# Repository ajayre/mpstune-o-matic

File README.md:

# mpstune-o-matic
D-Jetronic MPS Tune-o-Matic

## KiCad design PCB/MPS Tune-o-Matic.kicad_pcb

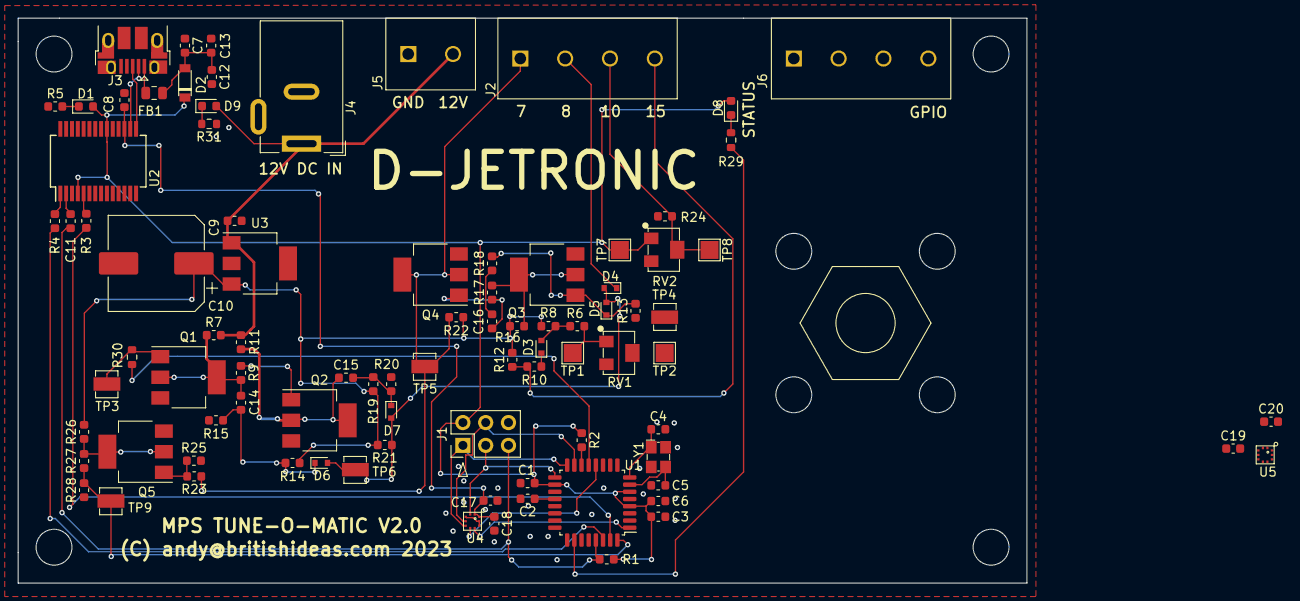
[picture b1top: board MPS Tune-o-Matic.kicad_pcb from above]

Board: 2 copper layers, 112.5 x 63.0 mm, 89 parts (0 on the bottom side), 54 nets.

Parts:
C1, C12: 4.7uF; C_0603_1608Metric
C2, C8, C11, C13, C17, C18, C19, C20: 100nF; C_0603_1608Metric
C3, C6: 1uF; C_0603_1608Metric
C4, C5: 18pF; C_0603_1608Metric
C7: 10nF; C_0603_1608Metric
C9: 0.47uF; C_0603_1608Metric
C10: 22uF; CP_Elec_10x10.5
C14, C15: 6.8n; C_0603_1608Metric
C16: 1.0n; C_0603_1608Metric
D1, D8, D9: APT1608EC; LED_0603_1608Metric
D2: MBR0520LT1G; SOD-123
D3, D4, D5, D6, D7: RB520SM-30T2R; D_SOD-523
FB1: MI0805K400R-10; R_0805_2012Metric
J1: ISP; PinHeader_2x03_P2.54mm_Vertical
J2: MPS; PhoenixContact_COMBICON_PT_4
J3: USB_B_Micro; USB_Micro-B_Amphenol_10103594-0001LF_Horizontal
J4: 12V 1A IN (5.5/2.5); BarrelJack_Wuerth_6941xx301002
J5: 12V IN; PhoenixContact_COMBICON_MKDSN_2
J6: GPIO; PhoenixContact_COMBICON_PT_4
Q1, Q2, Q3, Q4, Q5: PZT2222A,115; SOT-223-3_TabPin2
R1, R2, R3, R4, R7, R11, R22, R24: 1k; R_0603_1608Metric
R5, R29: 150; R_0603_1608Metric
R6: 240; R_0603_1608Metric
R8: 1k2; R_0603_1608Metric
R9, R25, R27, R30: 10k; R_0603_1608Metric
R10: 2k2; R_0603_1608Metric
R12, R31: 510; R_0603_1608Metric
R13: 180k; R_0603_1608Metric
R14, R19: 130k; R_0603_1608Metric
R15, R20: 68k; R_0603_1608Metric
R16, R26: 2k; R_0603_1608Metric
R17: 2k4; R_0603_1608Metric
R18: 300; R_0603_1608Metric
R21: 100k; R_0603_1608Metric
R23: 20k; R_0603_1608Metric
R28: 12k; R_0603_1608Metric
RV1: 1k; Surface_Mount_Cermet_Trimmer_SM-42-43W
RV2: 5k; Surface_Mount_Cermet_Trimmer_SM-42-43W
TP1: AT1; TestPoint_Pad_2.0x2.0mm
TP2: AT2; TestPoint_Pad_2.0x2.0mm
TP3, TP5, TP6, TP9: 5194TR; 5190TR-Colored-Test-Point
TP4: 5195TR; 5190TR-Colored-Test-Point
TP7: BIAS1; TestPoint_Pad_2.0x2.0mm
TP8: BIAS2; TestPoint_Pad_2.0x2.0mm
U1: ATmega328P; LQFP-32_7x7mm_P0.8mm
U2: FT232RL; SSOP-28_5.3x10.2mm_P0.65mm
U3: LM2940; SOT-223
U4, U5: BMP390; LGA-2x2-10-pin
Y1: FA-238 16.0000MB-C3; FA-238

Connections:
+3V3: C8.1, C17.1, C18.1, C19.1, C20.1, U2.17, U4.1, U4.10, U5.1, U5.10
+5V: C1.1, C3.1, C6.1, D1.2, D2.1, D8.2, J1.2, J6.1, R1.1, R2.1, RV2.1, TP7.1, U1.4, U1.6, U1.18, U2.4, U2.20
+10V: C10.1, R8.2, R12.2, R14.2, R16.2, R19.2, R21.2, R22.2, R26.2, U3.3
+12V: C9.1, D9.2, J4.1, J5.2, R7.2, R11.2, U3.1
/INT_PRESSURE: U1.1, U4.7
/INT_VAC_PRESSURE: U1.2, U5.7
/MISO: J1.1, U1.16, U4.5, U5.5
/MOSI: J1.4, U1.15, U4.4, U5.4
/MPS Stimulator/AUX11-TGL: C15.1, Q2.2, R11.1
/MPS Stimulator/AUX12-TGL: C14.1, Q1.2, R7.1, R9.2
/MPS Stimulator/EDGES: D4.2, D5.2, D6.2, D7.2, R21.1, TP6.1
/MPS-7: J2.1, Q4.2, R22.1, R23.1, TP5.1
/MPS-8: D4.1, J2.2
/MPS-10: J2.3, R24.2, RV2.2, TP8.1
/MPS-15: J2.4, R10.1, R12.1
/MPS_PULSE: R27.1, R28.2, TP9.1, U1.32
/MPS_STIMULUS: R30.2, U1.13
/RX: R4.2, U2.1
/SCK: J1.3, U1.17, U4.2, U5.2
/STATUS: R29.1, U1.26
/TX: R3.2, U2.5
/~CS_PRESSURE: U1.12, U4.6
/~CS_VAC_PRESSURE: U1.11, U5.6
/~RESET: C11.1, J1.5, R1.2, U1.29
GND: C1.2, C2.2, C3.2, C4.2, C5.1, C6.2, C7.1, C8.2, C9.2, C10.2, C12.2, C13.2, C17.2, C18.2, C19.2, C20.2, J1.6, J3.4, J3.5, J3.6, J4.2, J4.3, J5.1, J6.4, Q1.3, Q2.3, Q3.3, Q4.3, Q5.3, R5.1, R13.1, R15.1, R20.1, R24.1, R25.2, R28.1, R31.1, RV1.2, TP2.1, TP4.1, U1.3, U1.5, U1.21, U2.7, U2.18, U2.21, U2.25, U2.26, U3.2, U3.4, U4.3, U4.8, U4.9, U5.3, U5.8, U5.9, Y1.2, Y1.4
unnamed: C2.1, U1.20
unnamed: C4.1, U1.8, Y1.1
unnamed: C5.2, U1.7, Y1.3
unnamed: C11.2, U2.2
unnamed: C14.2, D6.1, R14.1, R15.2
unnamed: C15.2, D7.1, R19.1, R20.2
unnamed: C16.1, Q4.1, R17.1
unnamed: C16.2, R18.1
unnamed: D1.1, R5.2
unnamed: D3.1, R10.2
unnamed: D3.2, R6.1, R8.1
unnamed: D5.1, Q3.1, R13.2, R18.2
unnamed: D8.1, R29.2
unnamed: D9.1, R31.2
unnamed: FB1.1, J3.1
unnamed: J3.2, U2.16
unnamed: J3.3, U2.15
unnamed: J6.2, U1.10
unnamed: J6.3, U1.9
unnamed: Q1.1, R30.1, TP3.1
unnamed: Q2.1, R9.1
unnamed: Q3.2, R16.1, R17.2
unnamed: Q5.1, R23.2, R25.1
unnamed: Q5.2, R26.1, R27.2
unnamed: R2.2, U1.14
unnamed: R3.1, U1.31
unnamed: R4.1, U1.30
unnamed: R6.2, RV1.1, TP1.1
VBUS: C7.2, C12.1, C13.1, D2.2, FB1.2

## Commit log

2021-12-06 Started schematic.
2021-12-07 WIP.
2021-12-13 Working on KiCAD simulation of pressure loop to determine what the inputs are.
2021-12-14 Wprking on simulation of pressure loop.
2021-12-14 Using a real coupling factor for MPS.
2021-12-15 Added component for MPS.
2022-02-17 Updated MPS model for simulation.
2022-02-18 Added more simulation scenarios.
2022-02-18 Added waveforms and schematic diagram images. Added description.
2022-02-18 Added annotated schematics.
2022-02-18 MPS stimulation simulation.
2022-02-18 Added ideas document.
2022-02-20 Generates a 0-5V output.
2022-02-20 Completed stimulator. Added example waveforms.
2022-02-21 Completed schematic. Started work on PCB.
2022-02-23 Working on PCB layout.
2022-02-24 Completed PCB layout.
2022-02-25 Working on case.
2022-02-25 Moved DB9 connector and regenerated CAD files.
2022-02-25 Started case design.
2022-02-25 Changed LCD color.
2022-02-28 Pressure loop simulation now outputs dwell in degrees.
2022-03-01 Added simulation of contact bounce.
2022-10-31 Added status LED, remove LCD connectors, changed MPS connector to screw terminal block, added 12V power connections, removed 5V to 12V boost converter. Completely reworked PCB. Removed old PCB CAD fi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
2022-10-31 Generated CAD model of PCB.
2022-10-31 Deleted old case.
2022-10-31 Added new case.
2022-10-31 Added ground vias. Fixed voltage mistake for power LED.
2022-10-31 Added PCB manufacturing files.
2022-11-01 Added pressure sensor.
2022-11-01 Updated case and CAD model of PCB.
2022-11-01 Added case STL files.
2022-11-01 Added software notes.
2022-11-02 Updated 3D model - better screw terminals.
2022-11-02 Added Keyshot file.
2022-11-04 Updated Keyshot file to improve blue plastic.
2022-11-04 Started on firmware.
2022-11-04 Added flashing status LED.
2022-11-04 Moved firmware into named folder.
2022-11-05 Working on firmware - reports product UID and firmware version. Added libraries.
2022-11-06 Added BMP390 library. Added continuous measurements.
2022-11-07 Added initial MPS stimulation and measurement.
2022-11-10 Added LED for 12V power. Added resistor on MPS_STIMULUS signal. Moved track away from mounting hole. Fixed orientation of diodes. Added PDF of schematic. Updated manufacturing files.
2022-11-11 Added hole for 12V power LED in top of case.
2022-11-11 Flashes status LED faster when continuous measurement is enabled.
2022-11-12 Added calibration procedure.
2022-11-28 Added BOM and updated notes.
2023-09-29 Started work on V2.0 with vacuum monitoring.
2023-11-09 Fixed typos in calibration steps.
